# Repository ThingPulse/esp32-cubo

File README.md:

# ESP32-Cubo

The ESP32-Cubo is a device based on the Espressif ESP32 and comes with the following hardware:
- ESP32 Wrover-B Microcontroller module with 4MB Flash and 8MB SPIRAM memory
- Good Display 1.54" epaper display with 200x200 Black and White Pixels
- Battery charger and connector for LiPo battery
- USB connector for programming and charging
- CP2104 USB-to-Serial Chip
- 2x User controllable LEDs, red and green
- Inertial Measurement Unit ADXL345
- MAX17055 Fuel Gauge Chip for measuring battery voltage and estimating remaining capacity
- DS3231 Real Time Clock Chip for keeping time, powered by coin cell battery
- Reset Button

## Template for building a cardboard mockup
[Download cardboard template](/images/Cubo_Vorlage.pdf)

## Prerequisites
- esp32-cubo hardware
- usb cable to connect your computer to the device. 
- git installed on your command line
- experience in programming the ESP32 by using the Arduino platform

## Install the CP2102 driver

This driver is required to programm the esp32-cubo. It enables your computer to talk to the USB-to-Serial chip on the PCB.
To install the driver please follow the instructions under https://www.silabs.com/developers/usb-to-uart-bridge-vcp-drivers

## Setup Development environment

This sample code should in theory work with the Arduino IDE. Instead we suggest to use the Platformio IDE since it makes it
much easier to handle the correct libraries.

Platform IO IDE is a plugin for Microsoft's Visual Studio Code Editor. To install the Platformio IDE please follow
these instructions: https://platformio.org/install/ide?install=vscode

## Get the Code

To get the sample code run 

```
git clone https://github.com/thingpulse/esp32-cubo
```
from your command line or download the zip file from https://github.com/ThingPulse/esp32-cubo/archive/master.zip and unpack it. 

## Components Explained

### The ePaper Display

The 1.54" ePaper display has 200x200 black and white pixels. The display can maintain the state of the pixels even without
supporting power. This makes is a great tool for devices running from batteries since it only consumes energy during updates.

In this sample we use the ThingPulse Minigrafx library to control the display. You can find more information for programming
the display here: https://github.com/ThingPulse/minigrafx/blob/master/API.md

### The ADXL345 IMU

The ADXL345 chip can measure movement/accelereation in three axes. It can wakeup the main processor from deep sleep
when movement is detected. It can also be setup to detect taps  or double taps in one of the three axes. This repository
contains a slightly modified copy of a ADXL345 driver by Korneliusz Jarzebski

## Uploading Filesystem

In order to have the files under data/ available they need to be uploaded to the device first. Platformio creates a .bin file
which is then flashed to the device. Everytime you change the content under data/ this needs to be done. To this execute the following
task: env:esp-wrover-kit > Platform > Upload Filesystem Image

## Upload Code

To compile the code you can click on the checkmark icon in VS Code's footer. The arrow to the right will do the same and upload
the binary to the device. To plug icon turns on the serial console to monitor what is happening on the device.

## License

Copyright (c) 2020 - 2024, ThingPulse Ltd., Switzerland. All rights reserved.
Hardware is licensed under Creative Commons [CC BY-SA 4.0](https://creativecommons.org/licenses/by-sa/4.0/).
Software is licensed under MIT License, see [LICENSE](LICENSE).

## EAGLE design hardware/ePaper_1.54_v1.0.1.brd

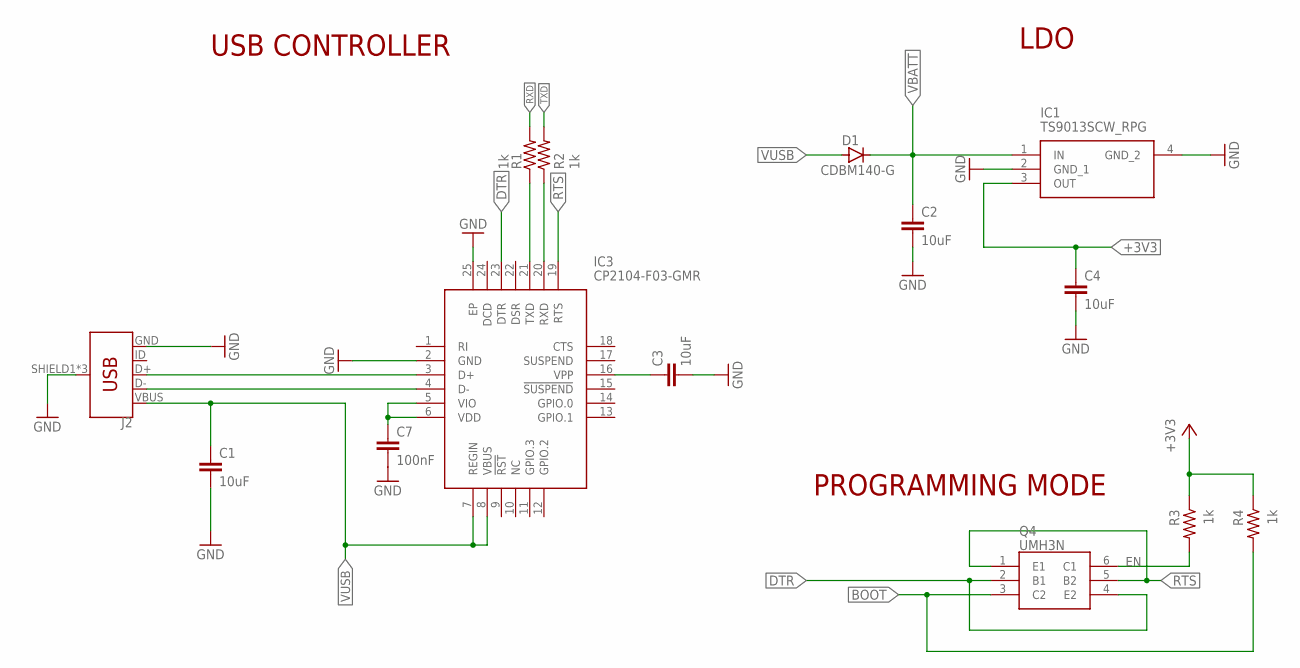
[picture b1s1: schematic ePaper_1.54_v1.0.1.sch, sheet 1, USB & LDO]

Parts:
C1, C2, C3, C4: 10uF; C0603
C7: 100nF; C0603
D1: CDBM140-G; SOD123
IC1: TS9013SCW_RPG; SOT230P700X180-4N
IC3: CP2104-F03-GMR; QFN50P400X400X80-25N
J2: USB_MICRO-B_FEMALE-SMT; USB-B-MICRO-SMD
Q4: UMH3N; SOT65P230X110-6N
R1, R2, R3, R4: 1k; R0603

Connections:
+3V3: C4.1, IC1.3 (OUT), R3.1, R4.1; also elsewhere on the board
BOOT: Q4.3 (C2), R4.2; also elsewhere on the board
DTR: IC3.23 (DTR), Q4.2 (B1), Q4.4 (E2)
EN: Q4.6 (C1), R3.2; also elsewhere on the board
GND: C1.2, C2.2, C3.2, C4.2, C7.2, IC1.2 (GND_1), IC1.4 (GND_2), IC3.2 (GND), IC3.25 (EP), J2.GND, J2.SHIELD1 (SHIELD), J2.SHIELD2 (SHIELD), J2.SHIELD3 (SHIELD); also elsewhere on the board
unnamed: IC3.3 (D+), J2.D+
unnamed: IC3.4 (D-), J2.D-
unnamed: C3.1, IC3.16 (VPP)
unnamed: C7.1, IC3.5 (VIO), IC3.6 (VDD)
unnamed: IC3.20 (RXD), R2.1
unnamed: IC3.21 (TXD), R1.1
RTS: IC3.19 (RTS), Q4.1 (E1), Q4.5 (B2)
RXD: R1.2; also elsewhere on the board
TXD: R2.2; also elsewhere on the board
VBATT: C2.1, D1.C, IC1.1 (IN); also elsewhere on the board
VUSB: C1.1, D1.A, IC3.7 (REGIN), IC3.8 (VBUS), J2.VBUS; also elsewhere on the board

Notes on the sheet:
USB CONTROLLER
LDO
PROGRAMMING MODE

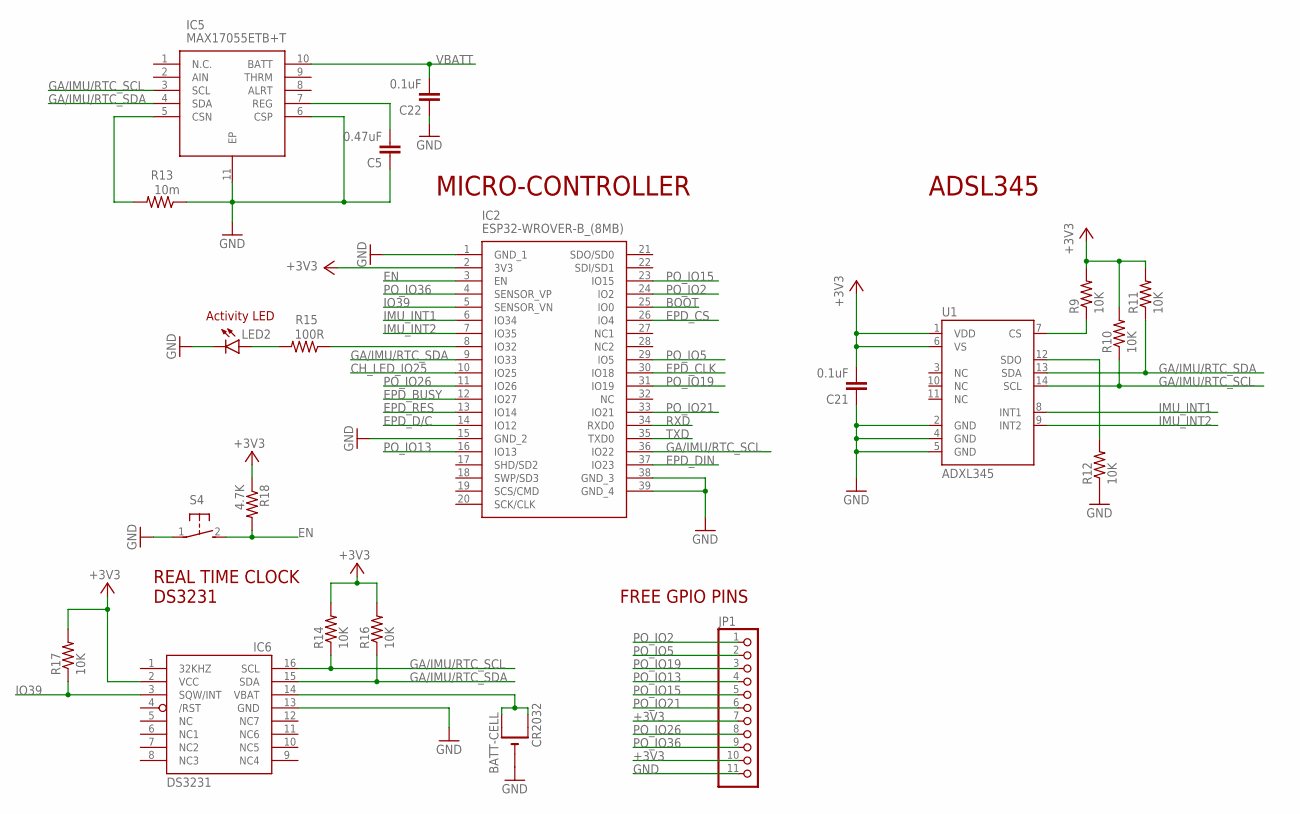
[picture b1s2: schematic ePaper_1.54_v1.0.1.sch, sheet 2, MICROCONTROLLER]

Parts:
BATT-CELL: CR2032; CR2032-SMD
C5: 0.47uF; C0603
C21, C22: 0.1uF; C0603
IC2: ESP32-WROVER-B_(8MB); ESP32WROVERIB8MB
IC5: MAX17055ETB+T; SON40P250X200X80-11N
IC6: DS3231/SO; SO16W
JP1: PINHD-1X11_2.54-S; 1X11-S
LED2: LEDCHIPLED_0805; CHIPLED_0805
R9, R10, R11, R12, R14, R16, R17: 10K; R0603
R13: 10m; R0603
R15: 100R; R0603
R18: 4.7K; R0603
S4: 31-XX; B3F-31XX
U1: ADXL345; LGA14

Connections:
+3V3: C21.2, IC2.2 (3V3), IC6.2 (VCC), JP1.7, JP1.10, R9.2, R10.2, R11.2, R14.2, R16.2, R17.2, R18.1, U1.1 (VDD), U1.6 (VS); also elsewhere on the board
BOOT: IC2.25 (IO0); also elsewhere on the board
CH_LED_IO25: IC2.10 (IO25); also elsewhere on the board
EN: IC2.3 (EN), R18.2, S4.2 (S); also elsewhere on the board
EPD_BUSY: IC2.12 (IO27); also elsewhere on the board
EPD_CLK: IC2.30 (IO18); also elsewhere on the board
EPD_CS: IC2.26 (IO4); also elsewhere on the board
EPD_D/C: IC2.14 (IO12); also elsewhere on the board
EPD_DIN: IC2.37 (IO23); also elsewhere on the board
EPD_RES: IC2.13 (IO14); also elsewhere on the board
GA/IMU/RTC_SCL: IC2.36 (IO22), IC5.3 (SCL), IC6.16 (SCL), R10.1, R14.1, U1.14 (SCL)
GA/IMU/RTC_SDA: IC2.9 (IO33), IC5.4 (SDA), IC6.15 (SDA), R11.1, R16.1, U1.13 (SDA)
GND: BATT-CELL.-, C5.1, C21.1, C22.1, IC2.1 (GND_1), IC2.15 (GND_2), IC2.38 (GND_3), IC2.39 (GND_4), IC5.6 (CSP), IC5.11 (EP), IC6.13 (GND), JP1.11, LED2.C, R12.1, R13.1, S4.1, U1.2 (GND), U1.4 (GND), U1.5 (GND); also elsewhere on the board
IMU_INT1: IC2.6 (IO34), U1.8 (INT1)
IMU_INT2: IC2.7 (IO35), U1.9 (INT2)
IO39: IC2.5 (SENSOR_VN), IC6.3 (SQW/INT), R17.1
unnamed: IC5.5 (CSN), R13.2
unnamed: C5.2, IC5.7 (REG)
unnamed: R12.2, U1.12 (SDO)
unnamed: R9.1, U1.7 (CS)
unnamed: BATT-CELL.+$1 (+), BATT-CELL.+$2 (+1), IC6.14 (VBAT)
unnamed: IC2.8 (IO32), R15.1
unnamed: LED2.A, R15.2
PO_IO2: IC2.24 (IO2), JP1.1
PO_IO5: IC2.29 (IO5), JP1.2
PO_IO13: IC2.16 (IO13), JP1.4
PO_IO15: IC2.23 (IO15), JP1.5
PO_IO19: IC2.31 (IO19), JP1.3
PO_IO21: IC2.33 (IO21), JP1.6
PO_IO26: IC2.11 (IO26), JP1.8
PO_IO36: IC2.4 (SENSOR_VP), JP1.9
RXD: IC2.34 (RXD0); also elsewhere on the board
TXD: IC2.35 (TXD0); also elsewhere on the board
VBATT: C22.2, IC5.10 (BATT); also elsewhere on the board

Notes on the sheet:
MICRO-CONTROLLER
ADSL345
Activity LED
FREE GPIO PINS
REAL TIME CLOCK DS3231

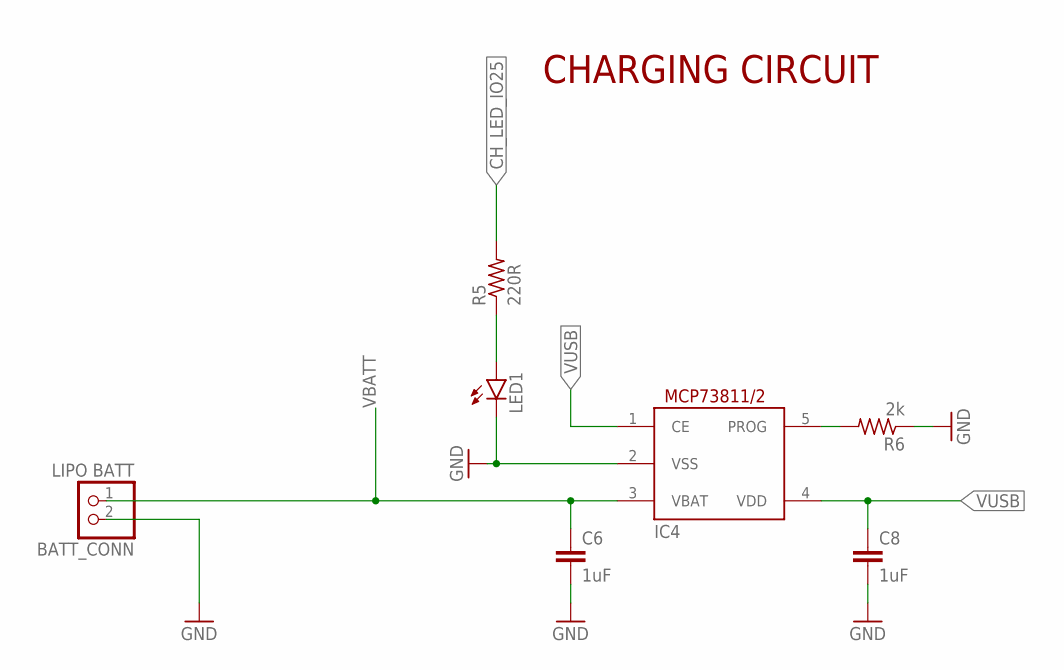
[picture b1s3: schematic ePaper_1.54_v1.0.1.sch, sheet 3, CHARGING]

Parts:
BATT_CONN: LIPO BATT; JST-PH-2-THM-RA
C6, C8: 1uF; C0805
IC4: MCP73811/2; SOT23-5L
LED1: LEDCHIPLED_0805; CHIPLED_0805
R5: 220R; R0603
R6: 2k; R0603

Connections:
CH_LED_IO25: R5.2; also elsewhere on the board
GND: BATT_CONN.2 (1), C6.2, C8.2, IC4.2 (VSS), LED1.C, R6.1; also elsewhere on the board
unnamed: IC4.5 (PROG), R6.2
unnamed: LED1.A, R5.1
VBATT: BATT_CONN.1 (2), C6.1, IC4.3 (VBAT); also elsewhere on the board
VUSB: C8.1, IC4.1 (CE), IC4.4 (VDD); also elsewhere on the board

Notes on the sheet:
CHARGING CIRCUIT

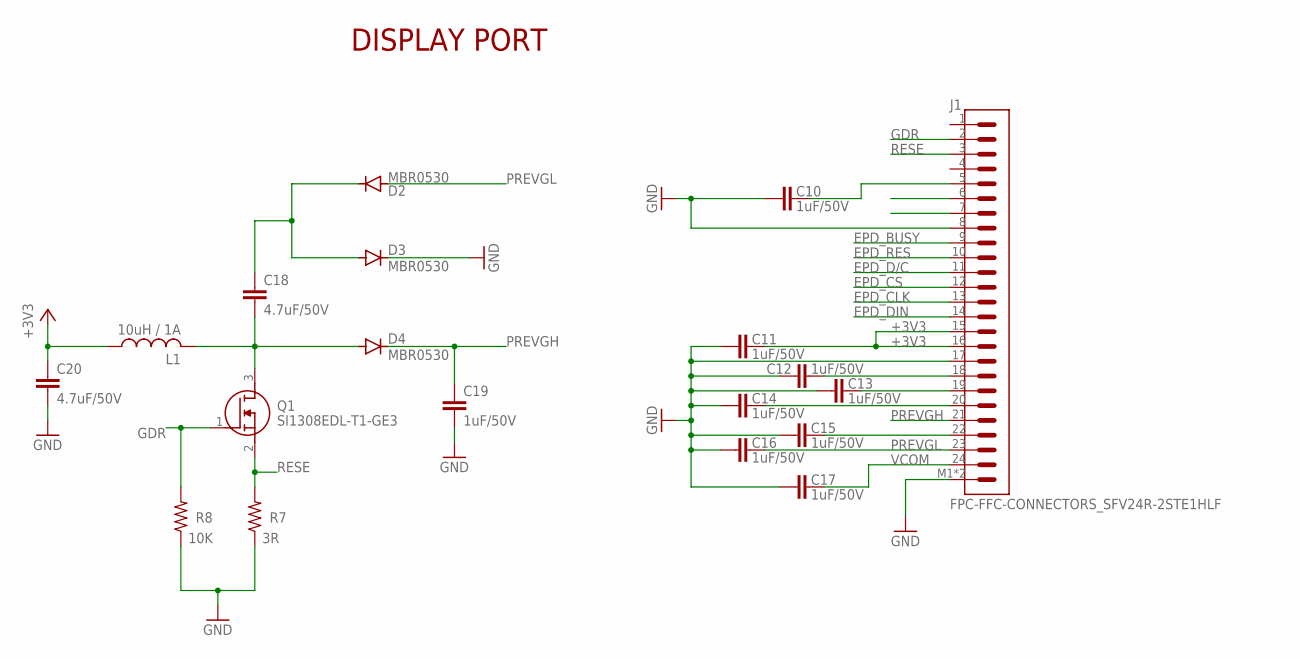
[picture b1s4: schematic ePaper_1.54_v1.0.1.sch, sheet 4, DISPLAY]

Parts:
C10, C11, C12, C13, C14, C15, C16, C17, C19: 1uF/50V; C0805
C18, C20: 4.7uF/50V; C0805
D2, D3, D4: MBR0530; SOD123
J1: FPC-FFC-CONNECTORS_SFV24R-2STE1HLF
L1: 10uH / 1A; L3225P
Q1: SI1308EDL-T1-GE3; SOT65P210X110-3N
R7: 3R; R0603
R8: 10K; R0603

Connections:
+3V3: C11.2, C20.2, J1.15, J1.16, L1.1; also elsewhere on the board
EPD_BUSY: J1.9; also elsewhere on the board
EPD_CLK: J1.13; also elsewhere on the board
EPD_CS: J1.12; also elsewhere on the board
EPD_D/C: J1.11; also elsewhere on the board
EPD_DIN: J1.14; also elsewhere on the board
EPD_RES: J1.10; also elsewhere on the board
GDR: J1.2, Q1.1 (G), R8.2
GND: C10.1, C11.1, C12.1, C13.1, C14.1, C15.1, C16.1, C17.1, C19.1, C20.1, D3.C, J1.8, J1.17, J1.M1 (SHIELD), J1.M2 (SHIELD), R7.1, R8.1; also elsewhere on the board
unnamed: C18.1, D4.A, L1.2, Q1.3 (D)
unnamed: C10.2, J1.5
unnamed: C18.2, D2.C, D3.A
unnamed: C12.2, J1.18
unnamed: C13.2, J1.19
unnamed: C14.2, J1.20
unnamed: C15.2, J1.22
PREVGH: C19.2, D4.C, J1.21
PREVGL: C16.2, D2.A, J1.23
RESE: J1.3, Q1.2 (S), R7.2
VCOM: C17.2, J1.24

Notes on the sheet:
DISPLAY PORT

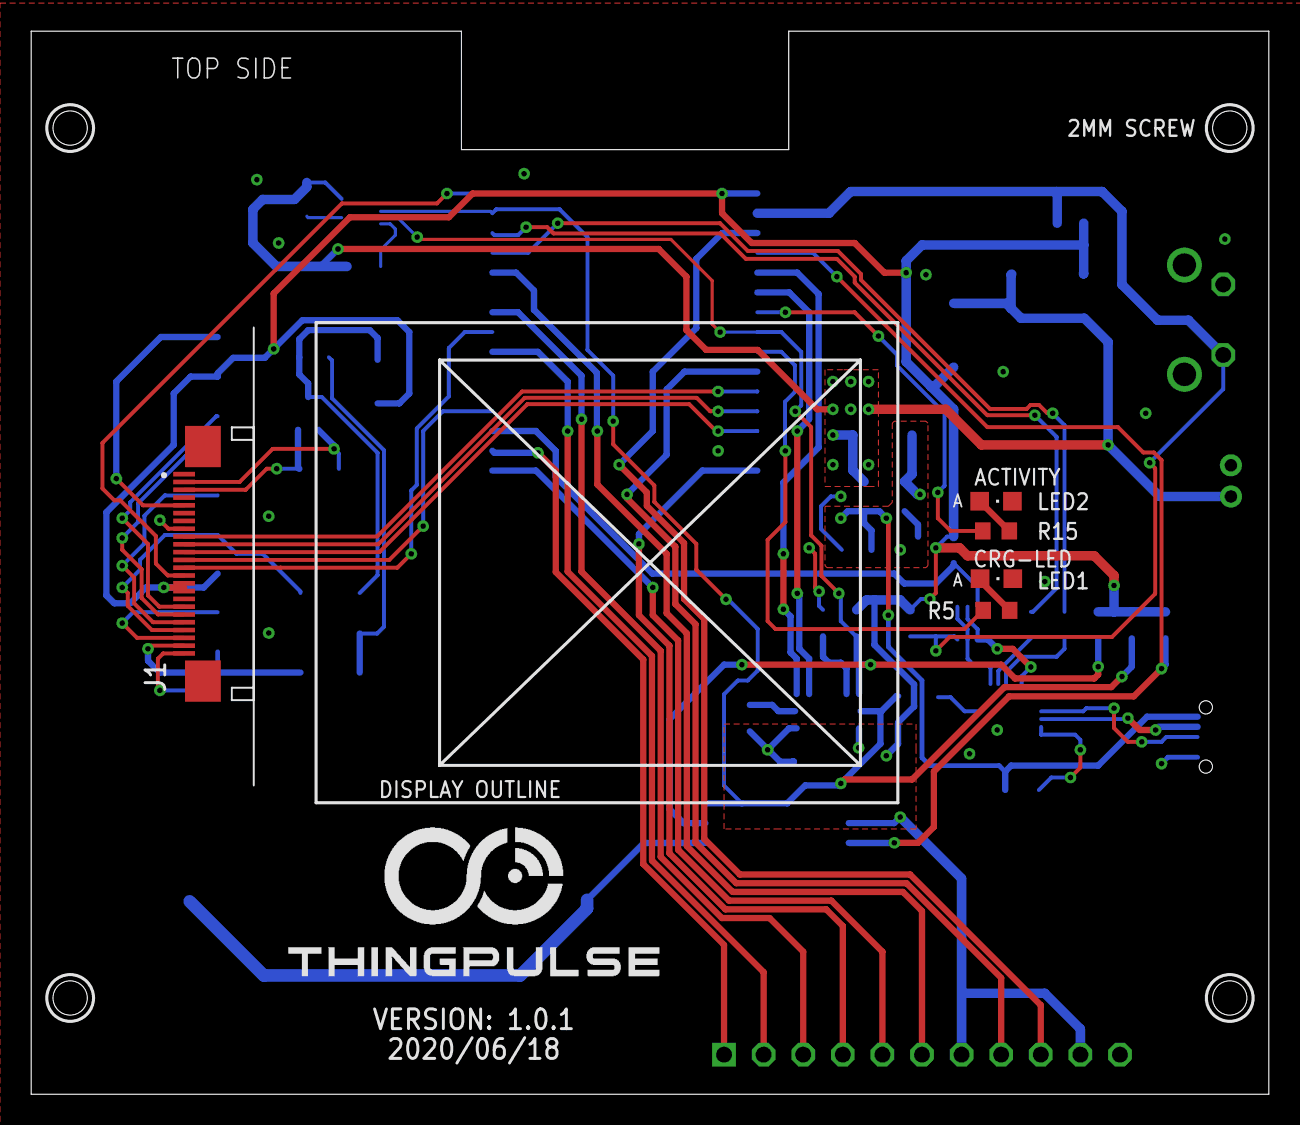
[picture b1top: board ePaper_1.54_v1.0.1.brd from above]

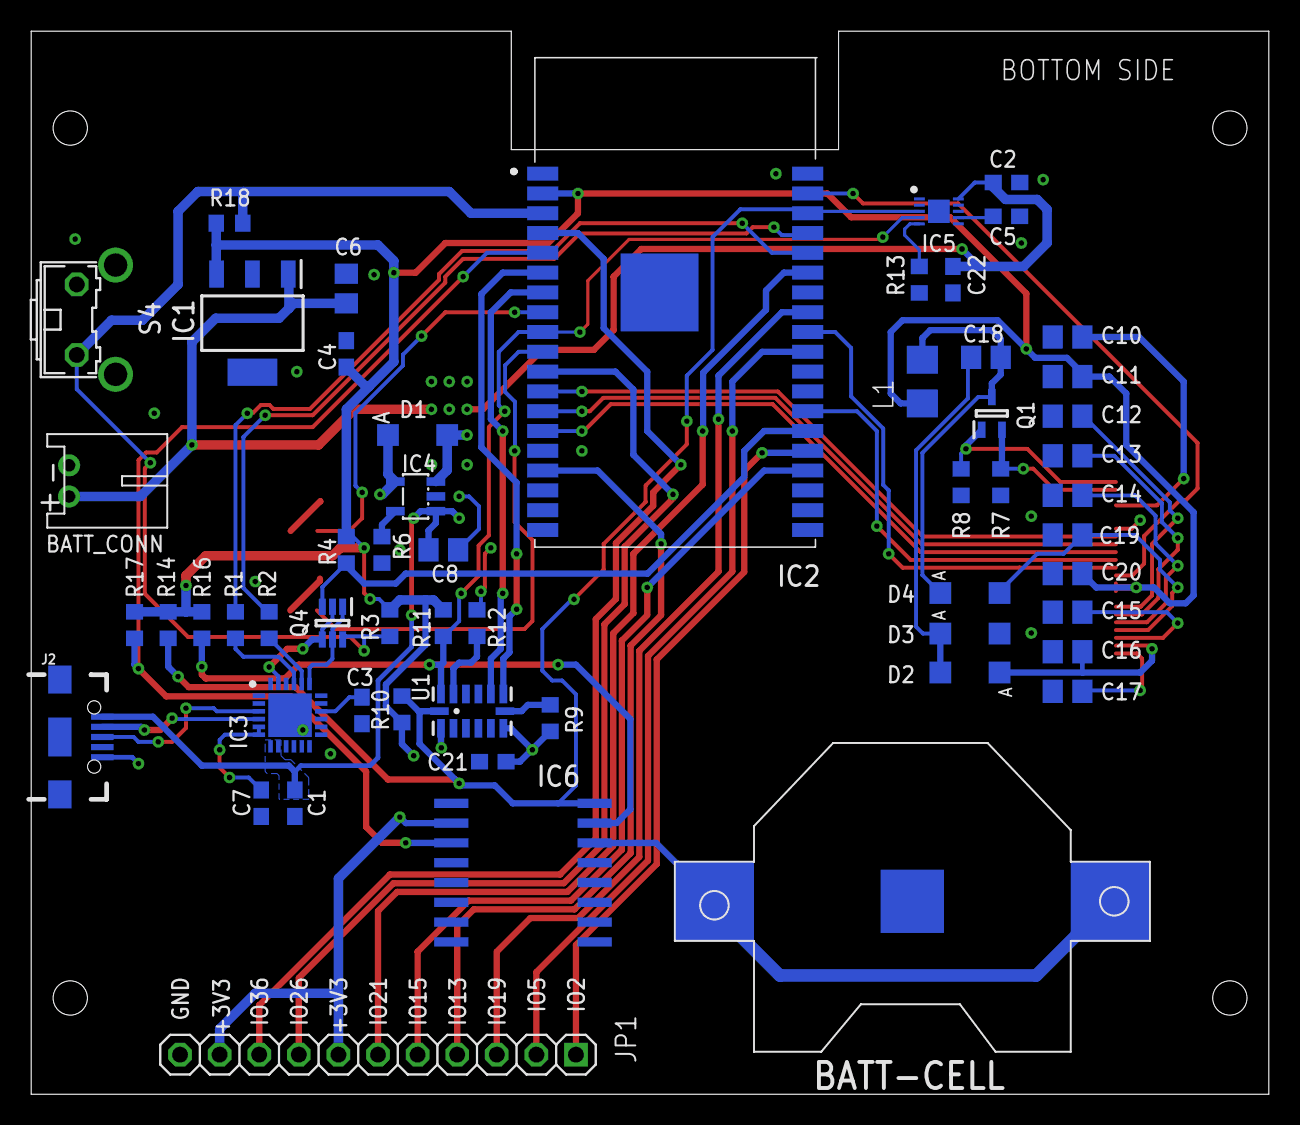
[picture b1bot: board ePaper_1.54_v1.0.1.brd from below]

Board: 2 copper layers, 79.4 x 68.2 mm, 61 parts (56 on the bottom side), 57 nets.

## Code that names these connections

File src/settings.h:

/*
MIT License

Copyright (c) 2020 ThingPulse GmbH

Permission is hereby granted, free of charge, to any person obtaining a copy
of this software and associated documentation files (the "Software"), to deal
in the Software without restriction, including without limitation the rights
to use, copy, modify, merge, publish, distribute, sublicense, and/or sell
copies of the Software, and to permit persons to whom the Software is
furnished to do so, subject to the following conditions:

The above copyright notice and this permission notice shall be included in all
copies or substantial portions of the Software.

THE SOFTWARE IS PROVIDED "AS IS", WITHOUT WARRANTY OF ANY KIND, EXPRESS OR
IMPLIED, INCLUDING BUT NOT LIMITED TO THE WARRANTIES OF MERCHANTABILITY,
FITNESS FOR A PARTICULAR PURPOSE AND NONINFRINGEMENT. IN NO EVENT SHALL THE
AUTHORS OR COPYRIGHT HOLDERS BE LIABLE FOR ANY CLAIM, DAMAGES OR OTHER
LIABILITY, WHETHER IN AN ACTION OF CONTRACT, TORT OR OTHERWISE, ARISING FROM,
OUT OF OR IN CONNECTION WITH THE SOFTWARE OR THE USE OR OTHER DEALINGS IN THE
SOFTWARE.
*/

#define BASE_URL "https://check.tempo-tag.com/"
#define URI_VERSION 1

// Does not just define the absolute *interval* but actually every nth interval of time. It behaves
// like */n in a cron expression. Example: 900s -> 15min => */15 => every 15th minute of every hour.
#define WAKEUP_INTERVAL_SECONDS 60
// Compensate for the seconds it takes to compile and upload the binary. Depends on the specific 
// machine the operation is executed on.
#define COMPILE_TIME_OFFSET_SECONDS 19
// The whole application uses UTC exclusively. The compile time, however, uses local system time.
#define UTC_OFFSET_SECONDS 7200

#define MINI_BLACK 0
#define MINI_WHITE 1

#define EPD_CS 4 
#define EPD_RST 14 
#define EPD_DC 12   
#define EPD_BUSY 27 
#define EDP_RES 14
#define EPD_DC 12
#define EPD_CLK 18
#define EPD_DIN 23

#define IMU_INT GPIO_NUM_36
#define IMU_SDA 15
#define IMU_SCL 13

#define GAUGE_SDA 33
#define GAUGE_SCL 22

#define RTC_SDA 33
#define RTC_SCL 22
#define RTC_INT GPIO_NUM_39

#define USR_LED_1 32
#define USR_LED_2 25

#define BITS_PER_PIXEL 1

#define countof(a) (sizeof(a) / sizeof(a[0]))

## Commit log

2020-11-26 Initial import
2020-11-26 Add IMU example code
2020-11-29 Use simplified sample
2020-11-29 Improve readme
2020-12-06 Use PNG images. Update readme
2020-12-10 Fix closing of png file. Add cubo image and template
2020-12-10 Fix images on repository
2020-12-11 Fix mockup type in README
2021-06-10 Add images and switch to jpg, remove PSRAM dependency (slower boot up)
2021-06-10 Added new resources
2024-05-16 Create LICENSE
2024-05-16 Add hardware license
2024-05-16 Add hardware design files

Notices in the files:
parts and their libraries:
SparkFun-Sensors: Licensing: Creative Commons ShareAlike 4.0 International - https://creativecommons.org/licenses/by-sa/4.0
